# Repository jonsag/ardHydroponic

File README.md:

# ardHydroponic

An Arduino Mega managing a hydroponic plant bed.  

Visualization on an LCD screen  
Managed and configured with push buttons  
Data uploaded to Blynk app and ThingSpeak  
Monitored on a webpage

## Hardware

Things marked as optional are used when you make a PCB and/or an ESP-01 module.  

1 x Arduino Mega 2560, [AliExpress](https://www.aliexpress.com/wholesale?SearchText=arduino+mega+2560)  

1 x LCD display, 4x20 with I2C communication, [AliExpress](https://www.aliexpress.com/wholesale?SearchText=lcd+4x20+i2c)  

1 x ESP-01 module, [AliExpress](https://www.aliexpress.com/wholesale?SearchText=esp-01) (optional)  

5 x Momentary push button [AliExpress](https://www.aliexpress.com/wholesale?SearchText=switch+dip+6mm)  

5 x MOSFET module, [AliExpress](https://www.aliexpress.com/wholesale?SearchText=mosfet+module+irf520)  

4 x pump, [AliExpress](https://www.aliexpress.com/wholesale?SearchText=peristaltic+pump)  

1 x magnetic stirrer, [DIY suggestion](https://www.instructables.com/How-to-Make-a-Cheap-Portable-Magnetic-Stirrer/)  

1 x EC/TDS sensor, [AliExpress](https://www.aliexpress.com/wholesale?SearchText=dfrobot+gravity+tds)  

1 x pH sensor, [AliExpress](https://www.aliexpress.com/wholesale?SearchText=dfrobot+gravity+ph)  

1 x DS18B20 temperature sensor, [AliExpress](https://www.aliexpress.com/wholesale?SearchText=ds18b20)  

1 x KY-019 relay module, [AliExpress](https://www.aliexpress.com/wholesale?SearchText=ky-019) (optional)  

5 x 10 kohm resistor  

1 x 4.7 kohm resistor  

1 x 1 kohm resistor (optional)  

1 x 2.2 kohm resistor (optional)  

1 x 2 pole screw terminal block, 5.0mm leg space [AliExpress](https://www.aliexpress.com/wholesale?SearchText=screw+terminal+block+5.0+mm) (optional)  

1 x 3 pole screw terminal block, 5.0mm leg space [AliExpress](https://www.aliexpress.com/wholesale?SearchText=screw+terminal+block+5.0+mm) (optional)  

1 x 5 pole screw terminal block, 5.0mm leg space [AliExpress](https://www.aliexpress.com/wholesale?SearchText=screw+terminal+block+5.0+mm) (optional)  

1 x 6 pole screw terminal block, 5.0mm leg space [AliExpress](https://www.aliexpress.com/wholesale?SearchText=screw+terminal+block+5.0+mm) (optional)  

1 x 4x2 pin socket header (optional)  

Some single row pin and socket headers, 100mil legs space (optional)  

1 x DC power source, same voltage as your pumps. If this will also feed the Arduino board, not higher than 12V  

A PCB like the one in [this gerber zip](KiCAD/ardHydroponic/Gerber/ardHydroponic.zip) (optional)  

Connect and build everything according to the [schematics](KiCAD/ardHydroponic/ardHydroponic.pdf) in KiCAD.  

Calibration fluids:  
pH: two solutions with known values, for example 4.00 and 7.00  (other values will also work)  
TDS: solution with known TDS value  

## Usage

Your setup will have five push buttons and one LCD display.  
Everything is monitored and adjusted from the LCD.  
A lot of output is also provided on the serial output from the Mega.  

### Modes

There are four major modes of the system:  

* Running...  
* Maintenance  
* Settings  
* Special  

Also there is a 'Reading...' mode that the system enters when measuring in 'Running...' mode, and an 'Uploading...' mode when uploading data to internet.  

You advance from one mode to the next by pushing and holding down 'Button 1' for one second.  
When you do this in 'Special' mode you loop back to 'Running...' mode again.  

### 'Running...' mode

Button number:  

1. Enter next mode  
   * Long press: enter next mode  
2. No function  
3. No function  
4. No function  
5. No function  

LCD shows measured values, and whether they're too low or too high  

### 'Maintenance' mode

Button number:  

1. Enter next mode/Toggle output
   * Long press: enter next mode  
   * Short press: start or stop the indicated output  
2. Select previous output
3. Select next output
4. No function
5. No function

LCD shows selected output  

### 'Settings' mode

Button number:  

1. Enter next mode/Save variable  
   * Long press: leave this mode and enter next  
   * Short press: save variable to EEPROM  
2. Select previous variable
3. Select next variable
4. Step down selected variable
5. Step up selected variable

There are seventeen variables available:

* Nutr pump time,   ms
* pH+ pump time,    ms
* pH- pump time,    ms
* Clean pumps time, ms
* Iteration time,   ms
* Stir time,        ms
* Stir interval,    ms
* pH low,           pH
* pH high,          pH
* TDS low,         ppm
* k value,    constant
* TDS factor, constant
* Neutral pH,       pH
* Acid pH,          pH
* Neutral voltage,  mV
* Acid voltage,     mV
* pH voltage offs., mV

The names are pretty self explanatory.  
However, the last seven of these will be further explained in the calibration section below.  

The second line on the LCD will show the variable name.  
Line three will show the value stored in EEPROM.  
Line four will show the new value you step up and down.  

Also lines three and four will show pH and TDS when applicable.  

There is some sanity checking done of these variables when changing them via the LCD, but beware of what you tap in.  

### 'Special' mode

Button number:  

1. Enter next mode/Run action  
   * Long press: leave this mode and enter next  
   * Short press: Run selected action  
2. Select previous action
3. Select next action
4. No function
5. No function

LCD shows selected action and action result  

#### Actions

* Interact with ESP module in serial monitor
* Clear EEPROM. On next restart the EEPROM will be rewritten with the default values from config
* Reset ESP module
* Reset whole system
* Toggle the serial debugging output. Will go back to the setting in config.h after a restart.
* Print the IP of the ESP module
* Print MAC address of the ESP module

## Calibration

### TDS value

Put the TDS sensor in a solution with a know TDS value.  

Enter 'Settings' mode.

Select the 'TDS factor' variable using 'Button 2' and 'Button 3'.  
Enter the TDS factor of your known solution using 'Button 4' and 'Button 5'.  
The TDS value on the left of the screen will be updated whenever you push those buttons.  
Save the new 'TDS factor' with a short press on 'Button 1'.  

Select the 'k value' variable using 'Button 2' and 'Button 3'.  
Step up and down 'k value' using 'Button 4' and 'Button 5'.  
The TDS value on the left of the screen will be updated whenever you push those buttons.  
When the TDS value shown on screen correlates with your known solution save the 'k value' with a short press on 'Button 1'.  

### pH value

Enter 'Settings' mode.  

Select the 'Neutral pH' variable using 'Button 2' and 'Button 3'.  
Enter the pH value of your known solution, ie the one with the higher pH, using 'Button 4' and 'Button 5'.  
Save the new value with a short press on 'Button 1'.  

Select the 'Acid pH' variable using 'Button 2' and 'Button 3'.  
Enter the pH value of your known solution, ie the one with the lower pH, using 'Button 4' and 'Button 5'.  
Save the new value with a short press on 'Button 1'.  

Put your pH sensor in the neutral solution.  
Select the 'Neutral voltage' variable using 'Button 2' and 'Button 3'.  
On the lower right of the screen you will now see the measured voltage from the pH sensor in millivolts. You can't change that. However, pressing 'Button 4' or 'Button 5' will update that measurement.  
When you get a solid reading, save the value with a short press on 'Button 1'.  

Put your pH sensor in the acid solution.  
Select the 'Acid voltage' variable using 'Button 2' and 'Button 3'.  
On the lower right of the screen you will now see the measured voltage from the pH sensor in millivolts. You can't change that. However, pressing 'Button 4' or 'Button 5' will update that measurement.  
When you get a solid reading, save the value with a short press on 'Button 1'.  

There is also a 'pH voltage offset' for further trimming.  

## Web interface

A simple web page shows last data read and ThingSpeak upload status.  

You can also disable an enable the outputs relay from the page.

You can find the IP address of the web server using the 'Special' mode.  

## Blynk app

The app shows latest values of the sensors.  

Also you can control the outputs relay from it.  

## Software configuration

All configuration is made in 'config.h'

The most interesting variables are:

### varNames

If you want it in your own language, change it here.  
Other LCD output is mostly found in 'LCD.h', but also in some other places. Sorry...  

### vars

These are the start values of the variables that can be edited from the LCD.  
If you change these after having having uploaded the sketch once, it will not be used since these are now read from EEPROM.  

### incs

The increments/decrements of the variables above.  
(How big should the jumps be when using buttons 'Button 4' and 'Button5'.)  

## Libraries and boards in Arduino IDE

Most can be installed from within the Arduino IDE, but look out for the liquid crystal library so you don't install the wrong one.  
Read below!  

### ESP8266 board library

Add [http://arduino.esp8266.com/stable/package_esp8266com_index.json](http://arduino.esp8266.com/stable/package_esp8266com_index.json) (as a text line), in Files->Preferences->Additional Boards Manager URLs:  

Then go to Tools->Board:...->Boards Manager...,search for esp8266 and install it.  

### LiquidCrystal_I2C

Don't install the LiquidCrystal_I2C library with Arduino IDE's library manager.  

Instead use the one from [https://github.com/fdebrabander/Arduino-LiquidCrystal-I2C-library](https://github.com/fdebrabander/Arduino-LiquidCrystal-I2C-library).  

### FTDebouncer

[https://github.com/ubidefeo/FTDebouncer](https://github.com/ubidefeo/FTDebouncer)  

### Blynk

[https://github.com/blynkkk/blynk-library](https://github.com/blynkkk/blynk-library)  

### ThingSpeak

[https://github.com/iobridge/thingspeak](https://github.com/iobridge/thingspeak)  

### NTPClient

[https://github.com/arduino-libraries/NTPClient](https://github.com/arduino-libraries/NTPClient)  

## Install and configure

### Create accounts for online visualizations

#### thingspeak

Get an account at [thingspeak.com](https://thingspeak.com).

Create a new channel with the fields:

* Field1: Temp
* Field2: pH
* Field3: TDS

Take note of your channel ID and write API key.  

#### blynk

Download [Blynk](https://play.google.com/store/apps/details?id=cc.blynk) to your phone.  

Open Blynk and create a new project.  

Add widget boxes:  

* Gauge, Temperature, Input: Virtual V0, scaled 0-30
* Gauge, pH, Input: Virtual V1, scaled 0-15
* Gauge, TDS, Input Virtual V2, scaled 0-4000
* Button, Enabled, Mode: Switch, Output: Virtual V3

In your mail you will have received the authorization token.  

### Arduino Mega

Compile and upload hydroponicBase/src/* with, for example, Platform IO.  

When uploading over USB you must open up the connection between D14 and RESET, ie remove the jumper JP1.

### ESP-01

Rename/copy hydroponicConnect/src/secrets.h.template to hydroponicConnect/src/secrets.h, and edit it with your own values/keys.  

Compile and upload hydroponicConnect/src/* with, for example, Platform IO.  

## Trouble shooting

### Resetting EEPROM to default values at every start

Edit ardHydroponic.ino  

Uncomment the line  

    //clearEEPROM();

and upload sketch.  

## Misc

### Useful programs

#### cu

A simple serial monitor  

Get serial output  
>$ cu -l /dev/ttyACM0 -s 9600

Exit with ~. (tilde dot)  

#### picocom

A more versatile serial monitor  

Get serial output  
>$ picocom -b 115200 /dev/ttyACM0 --omap crcrlf

Exit with Ctrl+a Ctrl+x  

### Links

EC sensor:  
[https://wiki.dfrobot.com/Gravity__Analog_TDS_Sensor___Meter_For_Arduino_SKU__SEN0244](https://wiki.dfrobot.com/Gravity__Analog_TDS_Sensor___Meter_For_Arduino_SKU__SEN0244)  

pH sensor:  
[https://wiki.dfrobot.com/Gravity__Analog_pH_Sensor_Meter_Kit_V2_SKU_SEN0161-V2](https://wiki.dfrobot.com/Gravity__Analog_pH_Sensor_Meter_Kit_V2_SKU_SEN0161-V2)  

### Screen shots

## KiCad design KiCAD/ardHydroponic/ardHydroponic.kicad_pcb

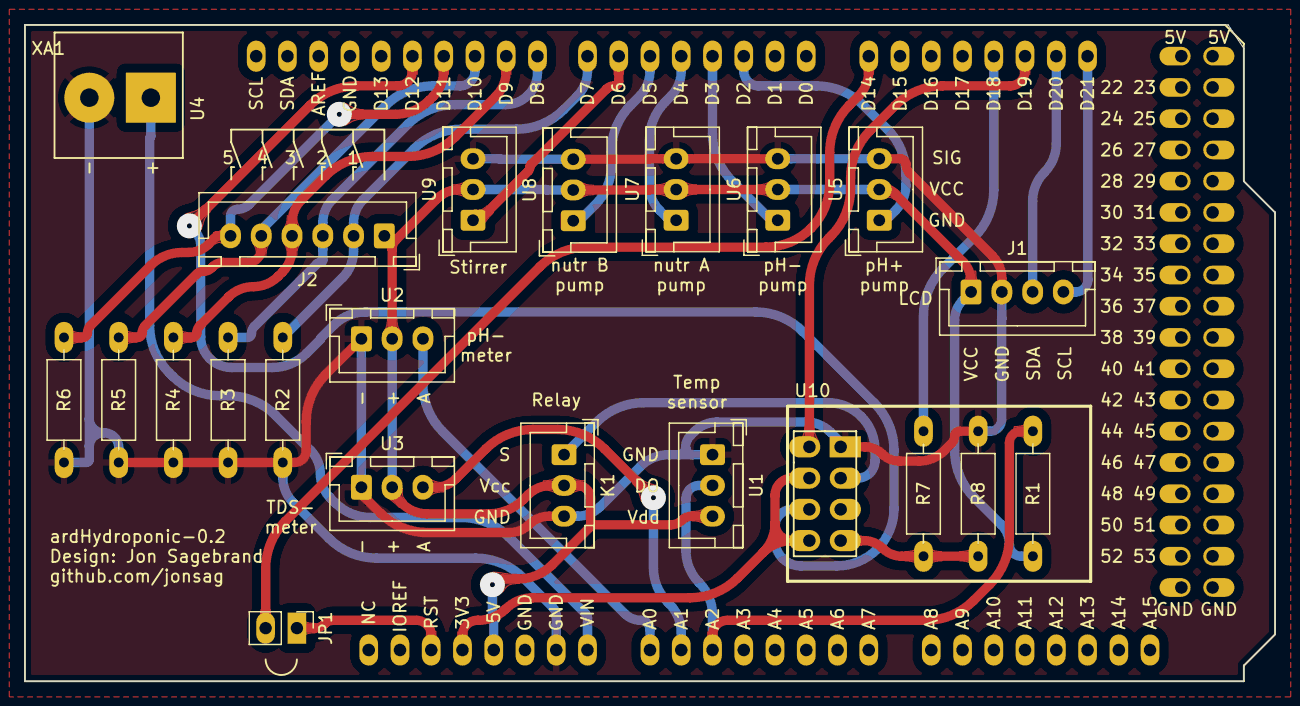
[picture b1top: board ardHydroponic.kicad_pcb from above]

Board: 2 copper layers, 101.6 x 53.3 mm, 23 parts (0 on the bottom side), 26 nets.

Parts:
J1: LCD 4x20; 4-pin JST LCD
J2: Buttons; 6-pin JST 5-buttons
JP1: Flash; Jumper_1x02_P2.54mm_large
K1: KY-019_relay_module; 3-pin JST KY-019 relay
R1: 4.7k; R_Axial_DIN0207_L6.3mm_D2.5mm_P10.16mm_Horizontal_larger_pa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
R2, R3, R4, R5, R6: 10k; R_Axial_DIN0207_L6.3mm_D2.5mm_P10.16mm_Horizontal_larger_pa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
R7: 1k; R_Axial_DIN0207_L6.3mm_D2.5mm_P10.16mm_Horizontal_larger_pa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
R8: 2.2k; R_Axial_DIN0207_L6.3mm_D2.5mm_P10.16mm_Horizontal_larger_pa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
U1: DS18B20; 3-pin JST DS18B20
U2: pH sensor; 3-pin JST pH Sensor
U3: TDS meter; 3-pin JST TDS Meter
U4: Power in; 2-pole_power_in_screw_terminal
U5: pH+ pump; 3-pin JST IRF520 MOSFET module
U6: pH- pump; 3-pin JST IRF520 MOSFET module
U7: nutr A pump; 3-pin JST IRF520 MOSFET module
U8: nutr B pump; 3-pin JST IRF520 MOSFET module
U9: stirrer; 3-pin JST IRF520 MOSFET module
U10: ESP-01; ESP-01_w_pin_socket_large
XA1: Arduino_Mega2560; Arduino_Mega2560_Shield__no_ICSP_no_mount-holes_large

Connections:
+3V3: U10.4 (CH_PD/CH_EN), U10.8 (VCC), XA1.3V3 (3.3V)
+5V: J1.1 (+5V), J2.1, K1.2 (+), R1.2, U1.3 (VDD), U2.2 (+), U3.2 (+), U5.2 (VCC), U6.2 (VCC), U7.2 (VCC), U8.2 (VCC), U9.2 (VCC), XA1.10 (5V)
GND: J1.2 (GND), K1.3 (-), R2.1, R3.1, R4.1, R5.1, R6.1, R8.2, U1.1 (GND), U2.1 (-), U3.1 (-), U4.2 (-), U5.3 (GND), U6.3 (GND), U7.3 (GND), U8.3 (GND), U9.3 (GND), U10.1 (GND), XA1.62 (GND)
unnamed: JP1.1 (A), XA1.30 (RESET)
unnamed: JP1.2 (B), XA1.64 (D14_TX3)
unnamed: R1.1, U1.2 (DQ), XA1.95 (A2)
unnamed: R7.2, R8.1, U10.7 (GPIO3/UORxD)
unnamed: U2.3 (A), XA1.97 (A0)
unnamed: U3.3 (A), XA1.96 (A1)
unnamed: U4.1 (+), XA1.100 (VIN)
unnamed: J1.4 (SCL), XA1.43 (D21_SCL)
unnamed: J1.3 (SDA), XA1.44 (D20_SDA)
Relay: K1.1 (S), U10.3 (GPIO2)
Rx: U10.2 (GPIO1/UOTxD), XA1.45 (D19_RX1)
Tx: R7.1, XA1.46 (D18_TX1)
button1: J2.2, R2.2, XA1.16 (D7)
button2: J2.3, R3.2, XA1.17 (D8)
button3: J2.4, R4.2, XA1.18 (D9)
button4: J2.5, R5.2, XA1.23 (D10)
button5: J2.6, R6.2, XA1.24 (D11)
espReset: U10.6 (Reset), XA1.25 (D12)
nutrA: U7.1 (SIG), XA1.1 (D4)
nutrB: U8.1 (SIG), XA1.5 (D5)
pH+: U5.1 (SIG), XA1.6 (D2_INT0)
pH-: U6.1 (SIG), XA1.7 (D3_INT1)
stirrer: U9.1 (SIG), XA1.15 (D6)

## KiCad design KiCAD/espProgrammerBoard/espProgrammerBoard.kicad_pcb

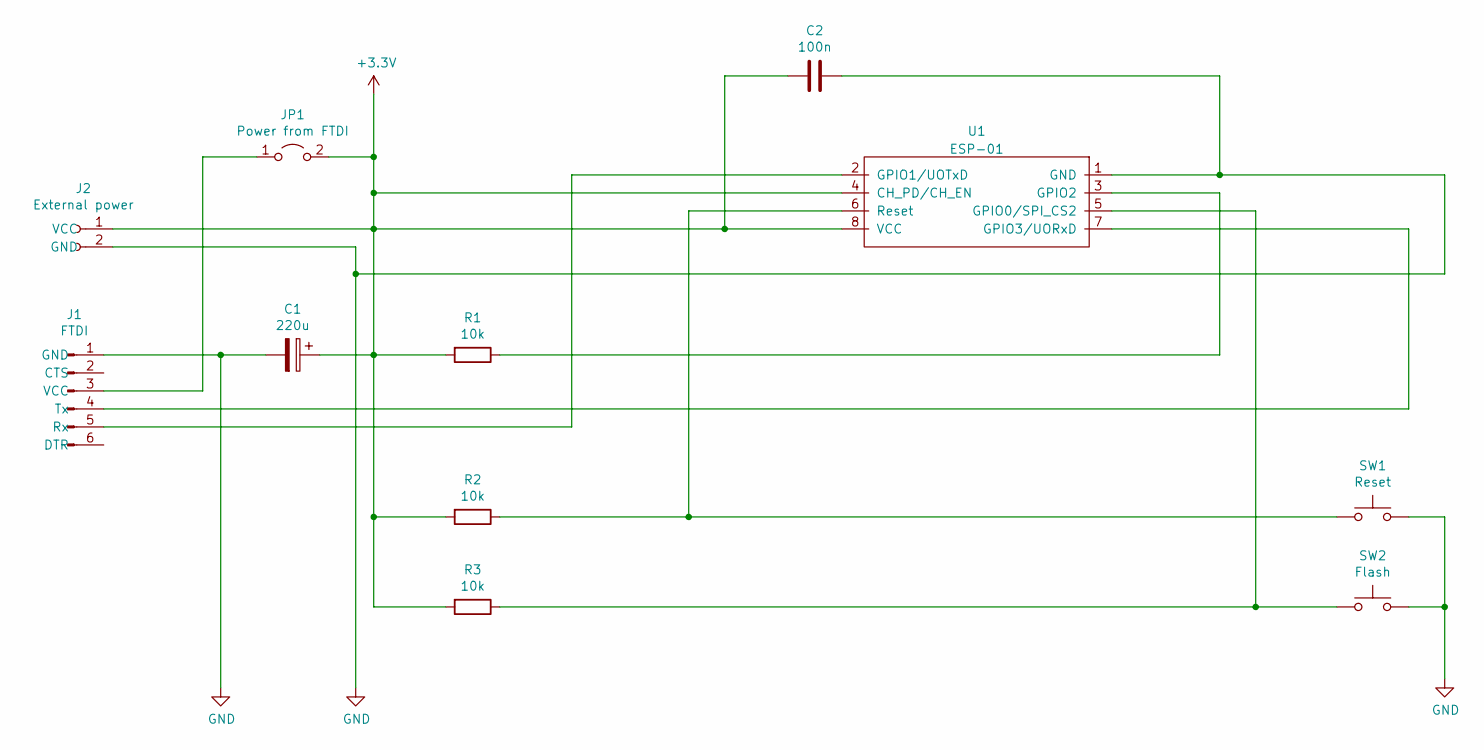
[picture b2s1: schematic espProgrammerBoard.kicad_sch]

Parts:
C1: 220u; CP_Radial_D6.3mm_P2.50mm_large
C2: 100n; C_Disc_D3.0mm_W1.6mm_P2.50mm_larg
J1: FTDI; 6-pin_FTDI_header_large
J2: External power; 2-pin_power_input_header_larger_pads
JP1: Power from FTDI; Jumper_1x02_P2.54mm_large
R1, R2, R3: 10k; R_Axial_DIN0207_L6.3mm_D2.5mm_P10.16mm_Horizontal_larger_pa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
SW1: Reset; SW_PUSH_6mm_large
SW2: Flash; SW_PUSH_6mm_large
U1: ESP-01; ESP-01_w_pin_socket_large

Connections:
+3V3: C1.1, C2.1, J2.1 (VCC), JP1.2 (B), R1.2, R2.2, R3.2, U1.4 (CH_PD/CH_EN), U1.8 (VCC)
GND: C1.2, C2.2, J1.1 (GND), J2.2 (GND), SW1.2, SW2.2, U1.1 (GND)
unnamed: J1.3 (VCC), JP1.1 (A)
unnamed: J1.4 (Tx), U1.7 (GPIO3/UORxD)
unnamed: J1.5 (Rx), U1.2 (GPIO1/UOTxD)
unnamed: R1.1, U1.3 (GPIO2)
unnamed: R2.1, SW1.1, U1.6 (Reset)
unnamed: R3.1, SW2.1, U1.5 (GPIO0/SPI_CS2)

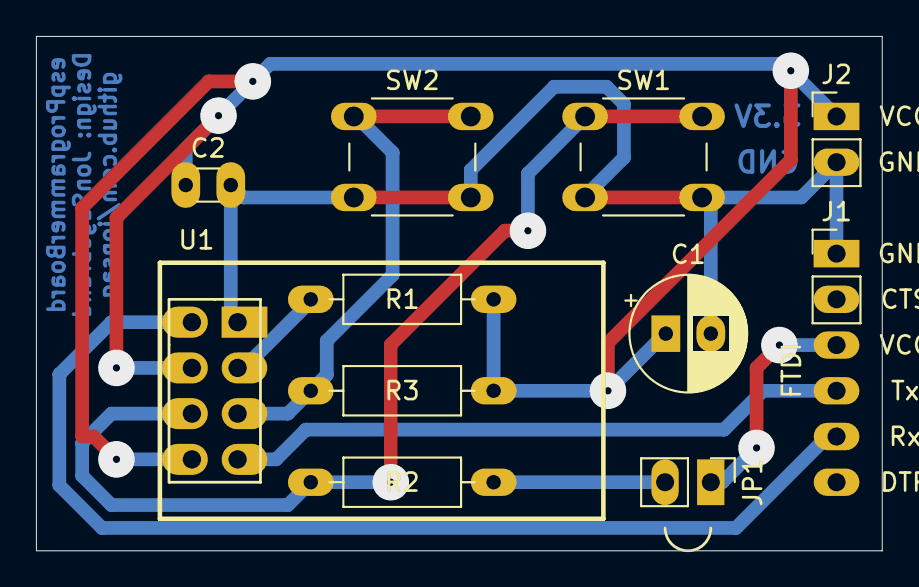
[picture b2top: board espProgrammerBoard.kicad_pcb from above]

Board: 2 copper layers, 47.0 x 28.6 mm, 11 parts (0 on the bottom side), 8 nets.

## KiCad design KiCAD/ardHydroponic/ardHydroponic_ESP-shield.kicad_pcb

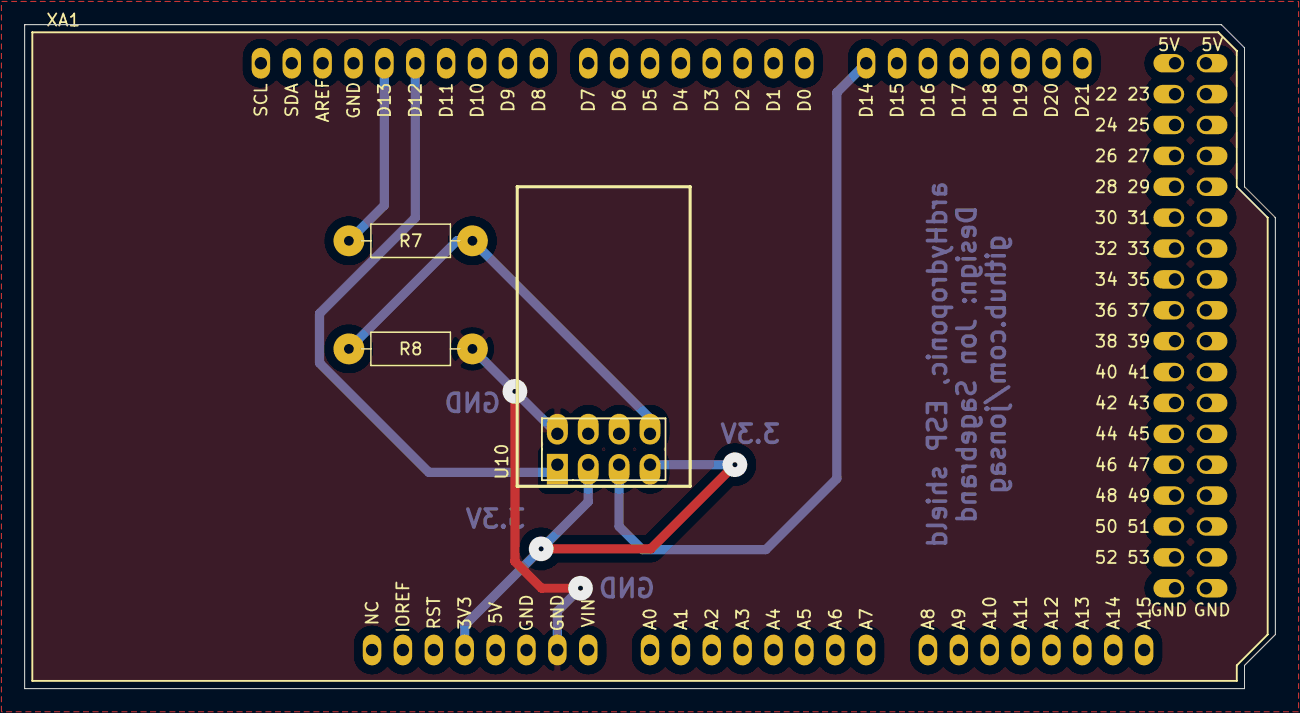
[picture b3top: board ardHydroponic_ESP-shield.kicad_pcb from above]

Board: 2 copper layers, 102.9 x 54.6 mm, 4 parts (0 on the bottom side), 6 nets.

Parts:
R7: 1k; R_Axial_DIN0207_L6.3mm_D2.5mm_P10.16mm_Horizontal_larger_pa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
R8: 2.2k; R_Axial_DIN0207_L6.3mm_D2.5mm_P10.16mm_Horizontal_larger_pa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
U10: ESP-01; ESP-01_large
XA1: Arduino_Mega2560; Arduino_Mega2560_Shield__no_ICSP_no_mount-holes_large

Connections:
+3V3: U10.3, U10.7, XA1.3V3
GND: R8.2, U10.2, XA1.62
unnamed: R7.2, R8.1, U10.8
espReset: U10.5, XA1.64
softRx: U10.1, XA1.25
softTx: R7.1, XA1.26

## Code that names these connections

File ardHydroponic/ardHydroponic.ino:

/**********
* Include files
**********/

#include "config.h"
#include "logging.h"
#include "LCD.h"
#include "outputs.h"
#include "read.h"
#include "misc.h"
#include "eeprom.h"
#include "specialMaint.h"
#include "buttons.h"

void setup()
{
  /***********
  * Serial
  ***********/
  Serial.begin(serialBaudRate); // serial baudrate

  /*******************************
  * Print start information
  *******************************/
  if (debug)
    Serial.println();
  if (debug)
    Serial.println(programName);
  if (debug)
    Serial.println(date);
  if (debug)
    Serial.print("by ");
  if (debug)
    Serial.println(author);
  if (debug)
    Serial.println(email);
  if (debug)
    Serial.println();

  /**********
  * LCD
  **********/
  if (debug)
    Serial.println("Starting LCD...");

  lcd.begin();
  if (debug)
    Serial.println();

  bootScreen(programName);
  bootScreen(date);

  /**********
  * EEPROM
  **********/
  //clearEEPROM();
  if (debug)
    Serial.println("Reading EEPROM...");
  bootScreen("Reading EEPROM...   ");

  initEEPROMCheck();
  if (debug)
    Serial.println();

  /**********
  * In/Outputs
  **********/
  if (debug)
    Serial.println("Starting In/Outputs...");
  bootScreen("Starting In/Outputs.");

  pinMode(pHPlusPump, OUTPUT);
  pinMode(pHMinusPump, OUTPUT);
  pinMode(nutrAPump, OUTPUT);
  pinMode(nutrBPump, OUTPUT);
  pinMode(stirrer, OUTPUT);

  pinMode(espHardwareReset, OUTPUT);

  digitalWrite(resetPin, HIGH); // set pin high before it's defined
  pinMode(resetPin, OUTPUT);

  if (debug)
    Serial.println();

  /**********
  * Setup FTDebouncer pins
  **********/
  if (debug)
    Serial.println("Setting up buttons...");
  bootScreen("Setting up buttons..");

  pinDebouncer.addPin(button1, LOW); // pin has external pull-down resistor
  pinDebouncer.addPin(button2, LOW);
  pinDebouncer.addPin(button3, LOW);
  pinDebouncer.addPin(button4, LOW);
  pinDebouncer.addPin(button5, LOW);

  pinDebouncer.init(); // initiate debounce

  if (debug)
    Serial.println();

  /**********
   * ESP-01
   **********/
  if (debug)
    Serial.println("Starting ESP-01...");
  bootScreen("Starting ESP-01...  ");

  digitalWrite(espHardwareReset, HIGH);
  if (debug)
    Serial.println();

  if (debug)
    Serial.println("Starting Serial1 for ESP communication...");
  bootScreen("Starting Serial1... ");

  Serial1.begin(serialBaudRate);
  if (debug)
    Serial.println();

  if (debug)
    Serial.println("Resetting ESP module...");
  bootScreen("Resetting ESP module");

  esp01HardwareReset();
  if (debug)
    Serial.println();

  /**********
  * Initiate screen
  **********/
  clearLCD();
  printNormal();
  readSensors();
}

void loop()
{
  currentMillis = millis();

  /**********
  * Read buttons
  **********/
  pinDebouncer.update();

  checkMode(); // check if mode has changed

  /**********
   * Count down on LCD
   **********/
  if (mode == 0)
  { // normal mode

    counter = (vars[4] - (currentMillis - readMillis)) / 1000;

    if ((counter != oldCounter) && (counter >= 0) && (counter <= readMillis / 1000))
    {
      printToLCD(17, 0, String(counter));
      printToLCD(17 + intLength(counter), 0, " ");

      /*
      if (counter <= 1)
      {
        if (debug) Serial.println("Powering EC sensor...");
        digitalWrite(ECPower, HIGH); // setting the power pin for EC sensor to high
      }
      */

      oldCounter = counter;
    }

    /**********
     * Upload data
     **********/
    if (currentMillis - readMillis > max(vars[0], max(vars[1], vars[2])) && newData)
    { // pumps has stopped
      mode = 2;
      checkMode();
      if (debug)
        Serial.println("Writing to Serial1...");
      writeToSerial1();
      //writeThingSpeak();
      mode = 0;
      checkMode();
      newData = 0;
    }

    /**********
    * Read loop
    **********/
    if (currentMillis - readMillis >= vars[4])
    { // read mode
      mode = 1;
      checkMode(); // check if mode has changed

      readSensors();

      mode = 0;    // go back to normal mode
      checkMode(); // check if mode has changed

      readMillis = millis();
    }

    /**********
    * Stirrer
    **********/
    if (currentMillis - stirStopMillis >= vars[6] && !digitalRead(stirrer))
    { // time to stir
      startStirrer();
      stirStartMillis = currentMillis;
    }

    checkOutputStop(); // check if it's time to stop the pumps or stirrer
  }
  else if (mode == 3)
  {                   // maintenance mode
    checkMaintStop(); // check if pumps are running and if it's time to stop any of them
  }
  else if (mode == 5)
  {
    doSpecialMaint();
  }

  if (button1PushMillis != 0 && currentMillis - button1PushMillis >= longPushTime)
  {
    button1PushMillis = 0;
    longPush = 1;
    longPushButton1();
  }
}

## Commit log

2021-03-07 sketch
2021-03-09 now working sketch
2021-03-12 moved values into variables
2021-03-12 screen bug
2021-03-13 readme
2021-03-13 rotary encoder
2021-03-13 more
2021-03-13 maint pump select
2021-03-14 maint pump starts
2021-03-14 reads and writes to eeprom
2021-03-15 started with buttons section
2021-03-15 exclude libraries, button long push
2021-03-16 excluded eeprom settings
2021-03-16 new routine for measuring EC
2021-03-16 bugs found
2021-03-16 tds -> EC
2021-03-16 nicer serial
2021-03-18 moved gravitytds into sketch
2021-03-18 time bug, stirrer
2021-03-18 variable names
2021-03-18 eeprom
2021-03-18 settings
2021-03-19 define stir output
2021-03-19 read and erase eeprom, stirrer
2021-03-19 deleted eeprom definition
2021-03-19 made tds library internal
2021-03-19 deletes
2021-03-19 moved variables into array
2021-03-19 serial output
2021-03-19 count tempValue up/down
2021-03-19 schematics
2021-03-20 new pins, schematics
2021-03-21 misplaced characters
2021-03-23 board layout
2021-03-23 deleted pcb
2021-03-24 bug, changed to float, settings partially implemen
2021-03-24 new schematics
2021-03-24 new PCB
2021-03-25 settings vars, saving to eeprom
2021-03-25 deleted some defs
2021-03-25 pH measuring
2021-03-25 settings, read temp before measure TDS
2021-03-26 new pH reading
2021-03-26 pH calibration, avarage readings
2021-03-29 KiCAD
2021-03-31 first test w esp and thingspeak
2021-03-31 ESP-shield
2021-04-04 logs to thingspeak
2021-04-05 plotting and debug selections in config
2021-04-05 new plot function
2021-04-05 too many commas
2021-04-05 kicad, programmer board
2021-04-05 text on copper
2021-04-06 new serial mode, can talk to ESP
2021-04-06 special, resets esp, clears EEPROM
2021-04-06 updated readme about new mode
2021-04-06 more readme
2021-04-06 code more modular
2021-04-06 installation instructions
2021-04-06 secrets template
2021-04-06 removed
2021-04-07 moved upload, upload info on LCD
2021-04-07 uploads when data is new and pumps has stopped
2021-04-07 nicer LCD
2021-04-07 special action to reset system
2021-04-07 links on readme
2021-04-08 esp in schematics
2021-04-08 pcb layout
2021-04-10 esp sketch
2021-04-10 buggy editor...
2021-04-10 now logs to thingspeak with own esp sketch
2021-04-11 blynk and webcontrol, relay output
2021-04-11 new board layout
2021-04-11 gerber
2021-04-12 ip view on esp
2021-04-12 cleaned up code
2021-04-13 debug config available. mac address show
2021-04-13 added jumper
2021-04-13 nicer webpage
2021-04-13 nicer LCD in maint
2021-04-13 blynk debig in espHydro...
2021-04-13 debug setting via serial on esp
2021-04-13 prints ip to LCD
2021-04-13 prints IP and MAC to LCD
2021-04-13 readme and pdf schematics
2021-04-13 new links in readme
2021-04-14 esp debugging
2021-04-15 minor bug
2021-04-15 scanning for networks
2021-04-15 blynk debug
2021-04-15 trying to print out wifi_station_get...()
2021-04-15 another try
2021-04-16 better debug
2021-04-17 moved to Platform IO
2021-04-17 deletions of .vscode
2021-04-17 more deletions
2021-04-17 pio settings
2021-04-21 pio configs
2021-04-21 scraps
2021-04-21 renamed readme
2021-04-22 function declarations
2021-04-22 forgot one
2021-10-03 readmes
2021-12-24 formatted
2022-05-13 kicad6
2022-05-13 programmer board
2023-02-21 kicad7
2025-04-28 kicad 8
